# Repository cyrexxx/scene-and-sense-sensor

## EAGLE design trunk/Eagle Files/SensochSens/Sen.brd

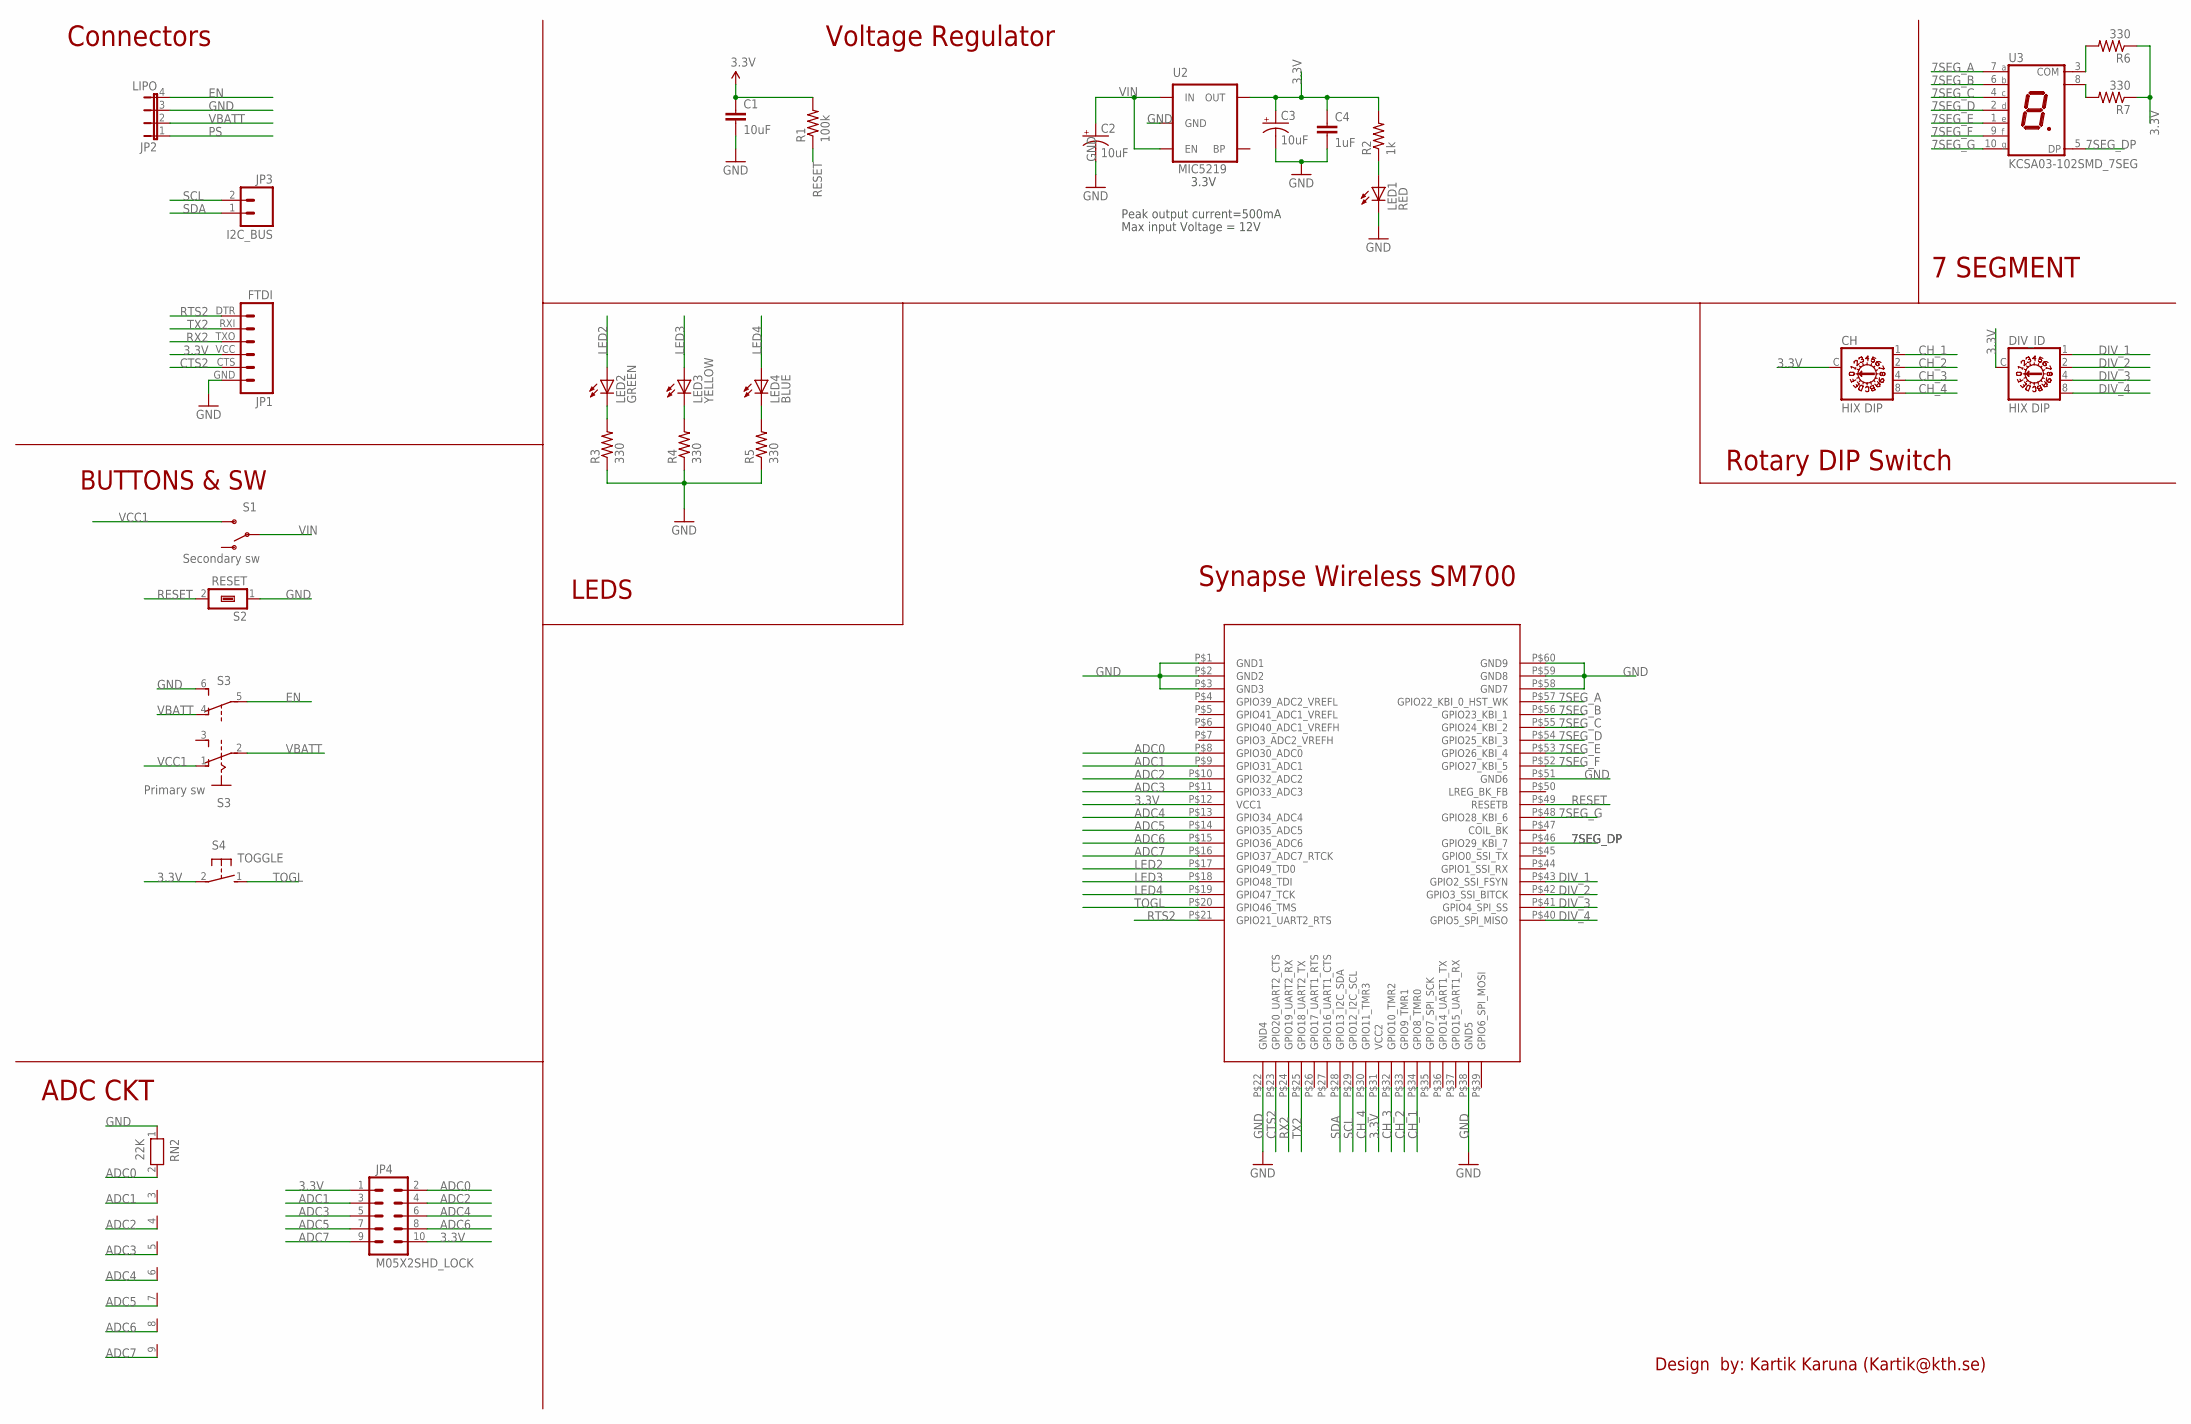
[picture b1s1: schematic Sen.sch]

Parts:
C1: 10uF; 0603-CAP
C2, C3: 10uF; EIA3528
C4: 1uF; 0402-CAP
CH: HIX DIP; A1353HEX
DIV_ID: HIX DIP; A1353HEX
JP1: FTDI; FTDI_BASIC
JP2: LIPO; JP4
JP3: I2C_BUS; 1X02_NO_SILK
JP4: M05X2SHD_LOCK; 2X5-SHROUDED_LOCK
LED1: RED; LED-0603
LED2: GREEN; LED-0603
LED3: YELLOW; LED-0603
LED4: BLUE; LED-0603
R1: 100k; 0805
R2: 1k; 0805
R3, R4, R5, R6, R7: 330; 0603-RES
RN2: 22K; RN-9
S1: Secondary sw; AYZ0202
S2: RESET; TYCO_FSM
S3: Primary sw; A68-A31
S4: TOGGLE; TYCO_FSMRACDA
U1: SM700PC1SMD; SYNAPSE_SN700PC1
U2: MIC5219; SOT23-5
U3: KCSA03-102SMD_7SEG; SMD-7SEG

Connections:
3.3V: C1.1, C3.A (+), C4.1, CH.C, DIV_ID.C, JP1.VCC (4), JP4.1, JP4.10, R1.2, R2.2, R6.1, R7.1, S4.2, U1.P$12 (VCC1), U1.P$31 (VCC2), U2.5 (OUT)
7SEG_A: U1.P$57 (GPIO22_KBI_0_HST_WK), U3.7 (A)
7SEG_B: U1.P$56 (GPIO23_KBI_1), U3.6 (B)
7SEG_C: U1.P$55 (GPIO24_KBI_2), U3.4 (C)
7SEG_D: U1.P$54 (GPIO25_KBI_3), U3.2 (D)
7SEG_DP: U1.P$46 (GPIO29_KBI_7), U3.5 (DP)
7SEG_E: U1.P$53 (GPIO26_KBI_4), U3.1 (E)
7SEG_F: U1.P$52 (GPIO27_KBI_5), U3.9 (F)
7SEG_G: U1.P$48 (GPIO28_KBI_6), U3.10 (G)
ADC0: JP4.2, RN2.2, U1.P$8 (GPIO30_ADC0)
ADC1: JP4.3, RN2.3, U1.P$9 (GPIO31_ADC1)
ADC2: JP4.4, RN2.4, U1.P$10 (GPIO32_ADC2)
ADC3: JP4.5, RN2.5, U1.P$11 (GPIO33_ADC3)
ADC4: JP4.6, RN2.6, U1.P$13 (GPIO34_ADC4)
ADC5: JP4.7, RN2.7, U1.P$14 (GPIO35_ADC5)
ADC6: JP4.8, RN2.8, U1.P$15 (GPIO36_ADC6)
ADC7: JP4.9, RN2.9, U1.P$16 (GPIO37_ADC7_RTCK)
CH_1: CH.1, U1.P$34 (GPIO8_TMR0)
CH_2: CH.2, U1.P$33 (GPIO9_TMR1)
CH_3: CH.4, U1.P$32 (GPIO10_TMR2)
CH_4: CH.8, U1.P$30 (GPIO11_TMR3)
CTS2: JP1.CTS (5), U1.P$23 (GPIO20_UART2_CTS)
DIV_1: DIV_ID.1, U1.P$43 (GPIO2_SSI_FSYN)
DIV_2: DIV_ID.2, U1.P$42 (GPIO3_SSI_BITCK)
DIV_3: DIV_ID.4, U1.P$41 (GPIO4_SPI_SS)
DIV_4: DIV_ID.8, U1.P$40 (GPIO5_SPI_MISO)
EN: JP2.4, S3.5
GND: C1.2, C2.C (-), C3.C (-), C4.2, JP1.GND (6), JP2.3, LED1.C, R3.1, R4.1, R5.1, RN2.1, S2.1, S3.6 (S), U1.P$1 (GND1), U1.P$2 (GND2), U1.P$3 (GND3), U1.P$22 (GND4), U1.P$38 (GND5), U1.P$51 (GND6), U1.P$58 (GND7), U1.P$59 (GND8), U1.P$60 (GND9), U2.2 (GND)
LED2: LED2.A, U1.P$17 (GPIO49_TD0)
LED3: LED3.A, U1.P$18 (GPIO48_TDI)
LED4: LED4.A, U1.P$19 (GPIO47_TCK)
unnamed: LED3.C, R4.2
unnamed: LED1.A, R2.1
unnamed: R6.2, U3.3 (COM)
unnamed: LED2.C, R3.2
unnamed: R7.2, U3.8 (COM)
unnamed: LED4.C, R5.2
PS: JP2.1
RESET: R1.1, S2.2, U1.P$49 (RESETB)
RTS2: JP1.DTR (1), U1.P$21 (GPIO21_UART2_RTS)
RX2: JP1.TXO (3), U1.P$24 (GPIO19_UART2_RX)
SCL: JP3.2, U1.P$29 (GPIO12_I2C_SCL)
SDA: JP3.1, U1.P$28 (GPIO13_I2C_SDA)
TOGL: S4.1, U1.P$20 (GPIO46_TMS)
TX2: JP1.RXI (2), U1.P$25 (GPIO18_UART2_TX)
VBATT: JP2.2, S3.2, S3.4 (O)
VCC1: S1.3 (S), S3.1 (O)
VIN: C2.A (+), S1.2, U2.1 (IN), U2.3 (EN)

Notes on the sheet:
Peak output current=500mA
3.3V
Max input Voltage = 12V
Design by: Kartik Karuna (Kartik@kth.se)
Connectors
Voltage Regulator
Synapse Wireless SM700
ADC CKT
LEDS
7 SEGMENT
Rotary DIP Switch
BUTTONS & SW

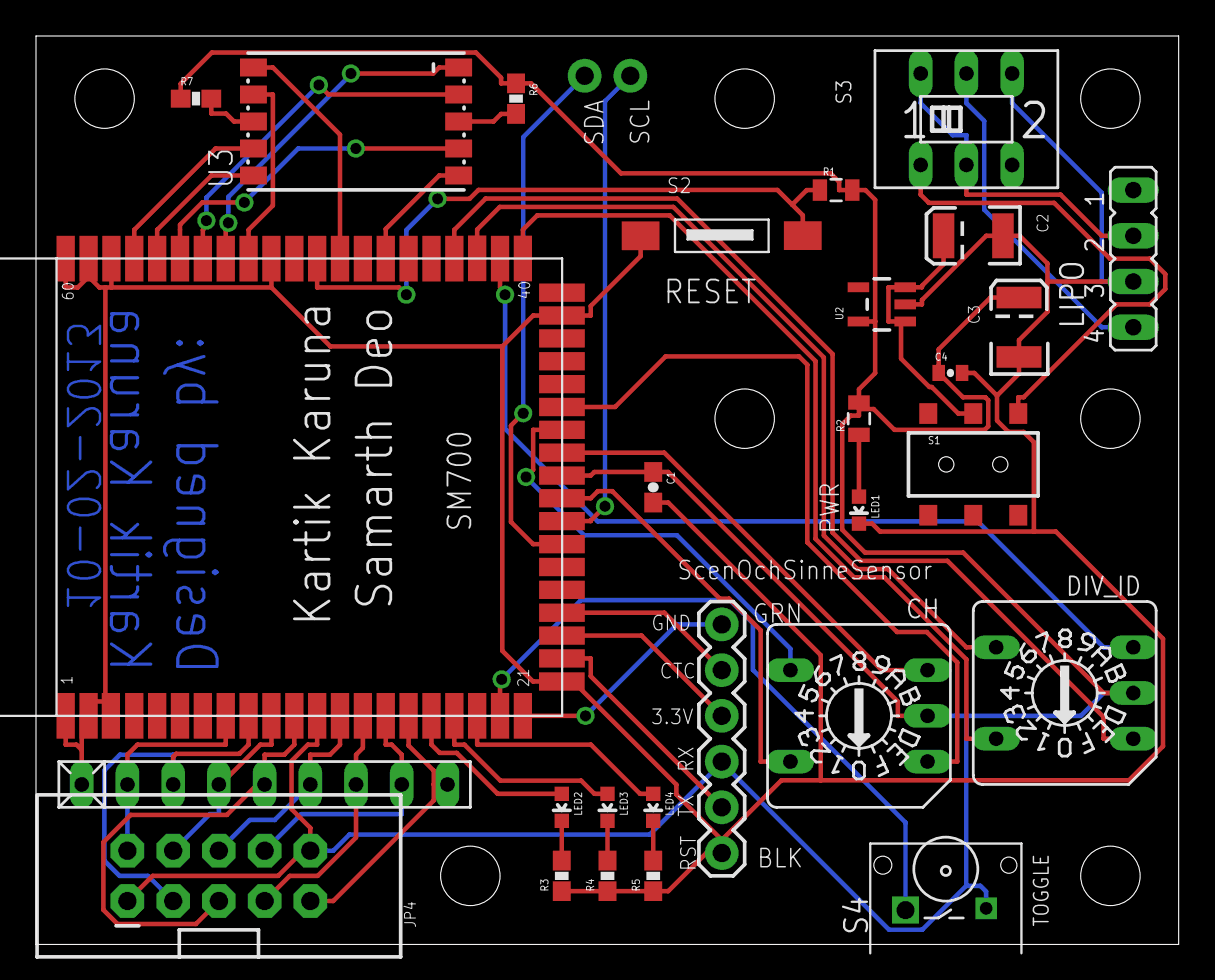
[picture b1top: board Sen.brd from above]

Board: 2 copper layers, 63.5 x 50.5 mm, 36 parts (0 on the bottom side), 47 nets.

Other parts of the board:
JP5, JP6, JP7, JP8, JP9, JP10, JP11: STAND-OFF

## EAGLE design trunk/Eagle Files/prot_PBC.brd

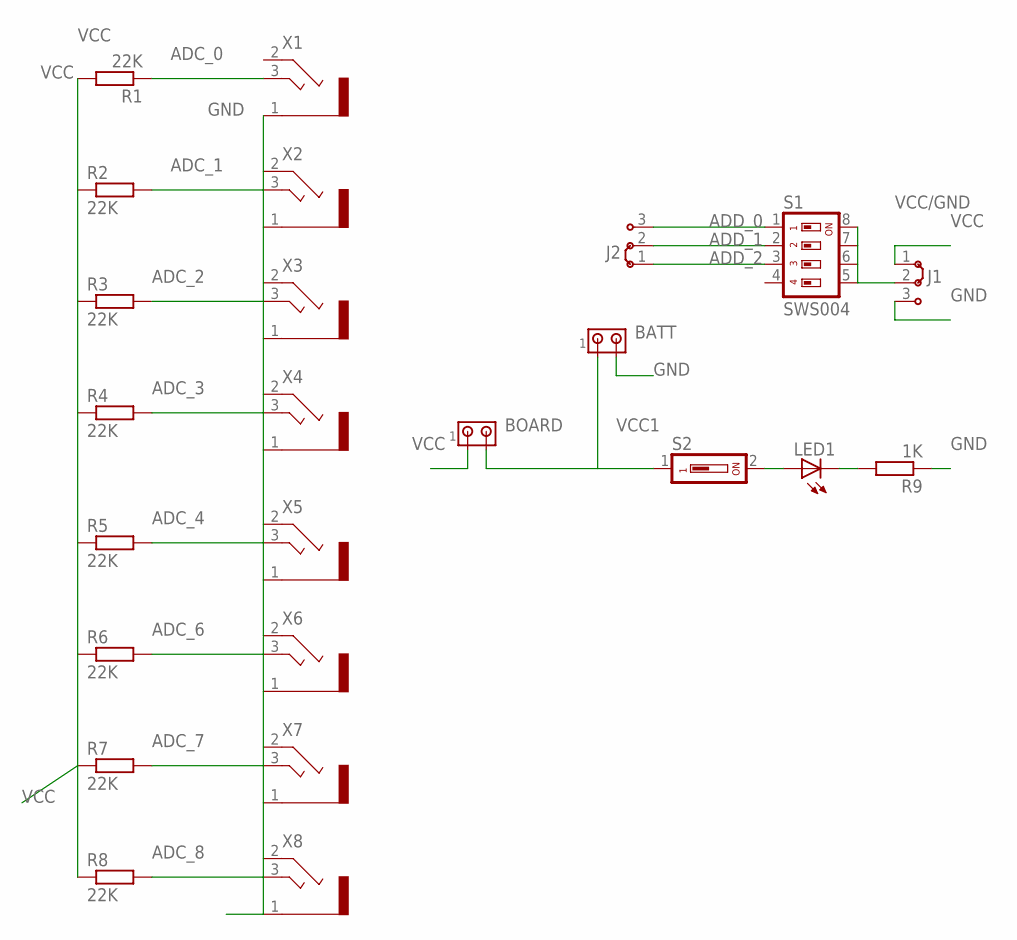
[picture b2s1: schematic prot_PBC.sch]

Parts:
BATT: MTA02-156; 1X2MTA
BOARD: MTA02-156; 1X2MTA
J1, J2: J2X2MM; 04C
LED1: LED5MM
R1, R2, R3, R4, R5, R6, R7, R8: 22K; 0207/7
R9: 1K; 0207/7
S1: SWS004; SMS-004
S2: DS01; DS-01
X1, X2, X3, X4, X5, X6, X7, X8: 1501_03

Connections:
ADC_0: R1.1, X1.3
ADC_1: R2.2, X2.3
ADC_2: R3.2, X3.3
ADC_3: R4.2, X4.3
ADC_4: R5.2, X5.3
ADC_6: R6.2, X6.3
ADC_7: R7.2, X7.3
ADC_8: R8.2, X8.3
ADD_0: J2.3, S1.1
ADD_1: J2.2, S1.2
ADD_2: J2.1, S1.3
GND: BATT.2, J1.3, R9.1, X1.1, X2.1, X3.1, X4.1, X5.1, X6.1, X7.1, X8.1
unnamed: LED1.K (C), R9.2
unnamed: LED1.A, S2.2
VCC: BOARD.1, J1.1, R1.2, R2.1, R3.1, R4.1, R5.1, R6.1, R7.1, R8.1
VCC1: BATT.1, BOARD.2, S2.1
VCC/GND: J1.2, S1.5, S1.6, S1.7, S1.8

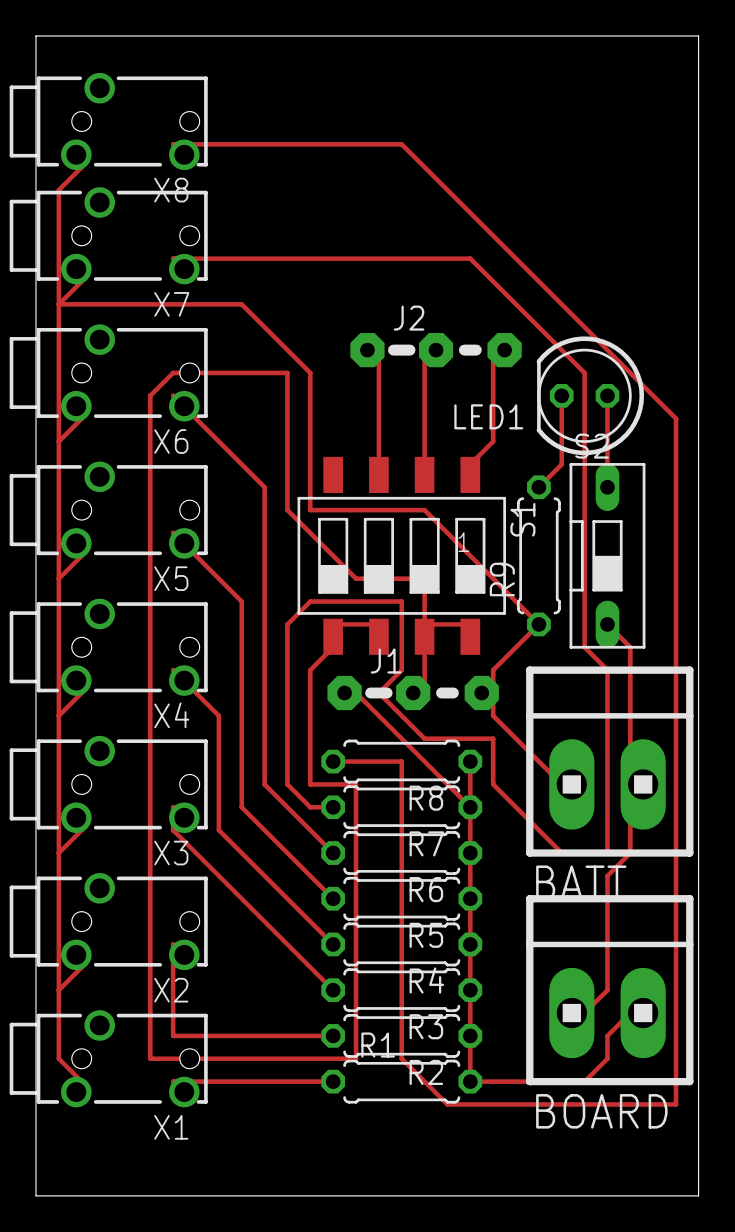
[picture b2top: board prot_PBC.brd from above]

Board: 2 copper layers, 36.8 x 64.4 mm, 24 parts (0 on the bottom side), 17 nets.

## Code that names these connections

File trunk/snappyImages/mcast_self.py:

"""/****************************************************************************
Title:    Slave device to read flexSensor values 
Author:   Kartik Karuna <kartik@kth.se>,Samarth Deo <samarthd@kth.se>
File:     $Id: Flex_slave.py ,v 1.2 2013/01/015 17:07:18 Kartik Exp $
Software: synapse IDE
Hardware: SM700 , Ver 2.4.33

Description:
    this code reads Analog values for 8 flex sensors and encodes it 
    into one message and sends it over the air to the Server  
Include Files (Libs)
     synapse.evalBase 
     synapse.nvparams 
*****************************************************************************/"""

serverAddr = '\x00\x00\x01' # hard-coded address for Portal PC

# Sensor connection PINs on board.
flexSensor = (8,9,10,11,12,13,14,15)         #creating a table os strings.

# Device address bits, 3 bits in total from DIP switch

addrBit0 = 57
addrBit1 = 56
addrBit2 = 55


secondCounter = 0
buttonCount = 0

BUTTON_PIN = 26 # SW1

LED1 = 23
LED2 = 24
LED3 = 25
LED4 = 1


def makeInput(pin):
    setPinDir(pin, False)   # set direction of the pin as output
    setPinPullup(pin, True) # Power the pin for the DIP SW
    monitorPin(pin, True)   # Monitor for button press

@setHook(HOOK_STARTUP)
def startupEvent():
    """This is hooked into the HOOK_STARTUP event"""
    global buttonState, buttonTime
    global addreBits
    
    #findServer() ##in once server is ready 
     
    print "starting"
    # Set PIN directions and initialize
    makeInput(addrBit0)
    makeInput(addrBit1)
    makeInput(addrBit2)
    setRate(1)             # set rate of polling for buttons 

    # Initialize button-detect variables
    addreBits = buttonRead()

def findServer():
    z=1
#mcastRpc(1,5,'svrAddr')

def serverAt(addr):
    global serverAddr
    #serverAddr = addr[:]


@setHook(HOOK_GPIN)
def buttonEvent(pinNum, isSet):
    """Hooked into the HOOK_GPIN event"""
    global addreBits
    if pinNum == (addrBit0 or addrBit1 or addrBit2):
        addreBits = buttonRead()

def buttonRead():    
    return int(str(readPin(addrBit0))+str(readPin(addrBit1))+str(readPin(addrBit2)), 2)




def doEverySecond():
    """Tasks that are executed every second"""
    z=0
    #showButtonCount()

@setHook(HOOK_100MS)
def timer100msEvent(currentMs):
    """Hooked into the HOOK_100MS event"""
    #global flexSensor
    
    # Read in the Analog values from the Sensors

    # read 8 sensor values
    sens =  str(readAdc(flexSensor[0])) + str(readAdc(flexSensor[1]))+str(readAdc(flexSensor[2]))
    #sens +=  str(i) + ':' + str(readAdc(flexSensor[i])) + '.'
        
       
    inpstr = str(addreBits) + '#' + sens    # package the Values in to one msg
    print "sens  = % s"   % sens
    rpc(serverAddr, "logEvent", inpstr , 100)    # Send package to server, Invoke Log event Function on the server  
    sendData()

def sendData():
    global inpstr 
    hello ="hello from straignt" 
    mcastRpc(1,5,"logEvent",hello)
    
    
    # Use a LONG (> 1 second) button press as a "counter reset"
"""#if buttonState == False:
        if buttonCount > 0:
            if currentMs - buttonTime >= 1000:
                buttonCount = 0
                reportButtonCount()"""

def setButtonCount(newCount):
    """Set the new button count"""
    global buttonCount
    buttonCount = newCount
    #showButtonCount()

def reportButtonCount():
    """Report to others that button press took place"""
    global buttonCount
    #showButtonCount()
    mcastRpc(1,2,'setButtonCount',buttonCount)

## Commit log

2013-01-28 Initial directory structure.
2013-01-28 Updated slave code
2013-01-28 Folder re-structure
2013-01-28 Minor bugs
2013-01-28 Cheks
2013-01-28 GIPO pin read after start-up Event
2013-01-28 Removed Error at 57
2013-01-28 Removed bugs in loop/arrays. Compiles now
2013-01-28 Corrections
2013-01-28 NVParams
2013-01-29 Removing non-required things
2013-01-29 Added Mcast
2013-01-29 Redefined pin definitions and initialization
2013-01-29 Testing Different sample times
2013-01-29 i=0, str(i) still needs to be fixed, everything else working good.
2013-01-30 Removed Loops
2013-01-30 overriding R24 : Working at 10MS
2013-01-31 DIP Sw check
2013-01-31 DIP SW working
2013-01-31 Slave side done
2013-01-31 Master - RF to Serial
2013-01-31 Eagle Files
2013-02-01 Master untested
2013-02-02 Master
2013-02-02 Master working
2013-02-02 Slave Clean up
2013-02-02 Master Clean up
2013-02-02 Processing Files
2013-02-02 Final Clean up processing sketch
2013-02-02 Com MOn working
2013-02-05 something screwed up
2013-02-05 Sketch update. Working!!
2013-02-06 Now working for all the sensors.
2013-02-08 re doing the folders OLD files
2013-02-14 cleanup
2013-03-19 Master and Slave Clean up
2013-05-28 Layout PDF
2015-07-04 Migrating wiki contents from Google Code

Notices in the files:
parts and their libraries:
SparkFun-Aesthetics: Licensing: CC v3.0 Share-Alike You are welcome to use this library for commercial purposes.
